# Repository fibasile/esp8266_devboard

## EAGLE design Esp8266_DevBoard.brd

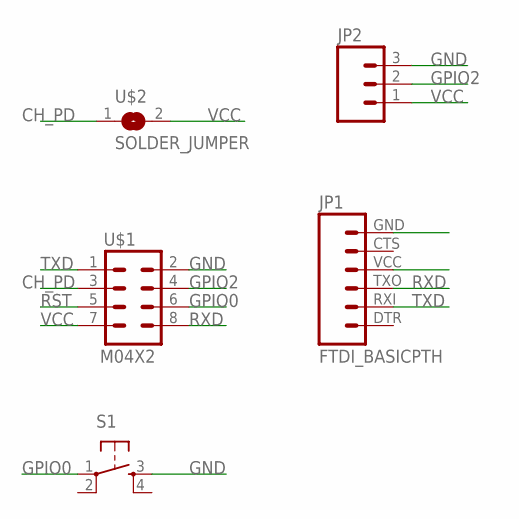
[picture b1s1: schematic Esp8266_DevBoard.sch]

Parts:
JP1: FTDI_BASICPTH; FTDI_BASIC
JP2: M03PTH; 1X03
S1: 6MM_SWITCH6MM_SWITCH; 6MM_SWITCH
U$1: M04X2; 2X4
U$2: SOLDER_JUMPER; SJFAB

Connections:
CH_PD: U$1.3, U$2.1
GND: JP1.GND (6), JP2.3, S1.3 (S), U$1.2
GPIO0: S1.1, U$1.6
GPIO2: JP2.2, U$1.4
RST: U$1.5
RXD: JP1.TXO (3), U$1.8
TXD: JP1.RXI (2), U$1.1
VCC: JP1.VCC (4), JP2.1, U$1.7, U$2.2

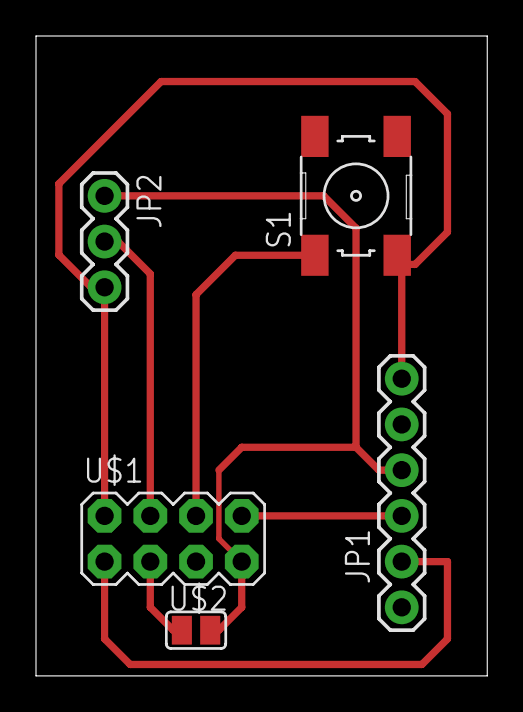
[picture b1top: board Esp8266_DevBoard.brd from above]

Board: 2 copper layers, 25.1 x 35.5 mm, 5 parts (0 on the bottom side), 7 nets.

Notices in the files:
parts and their libraries:
SparkFun-Connectors: Licensing: Creative Commons ShareAlike 4.0 International - https://creativecommons.org/licenses/by-sa/4.0
